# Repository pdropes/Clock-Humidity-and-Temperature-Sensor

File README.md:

# Clock, Humidity and Temperature Sensor
Relógio com medição de temperatura e humidade relativa

Descrição:
Pequeno aparelho portátil para visualização horária, temperatura e humidade relativa (alternadamente).
Já tinha trabalhado anteriormente com o sensor SHT21 da Sensirion, na construção de um controlador de estufa, é pequeno 3x3mm mas tem uma boa resolução (12/14bit for RH/T = RH0.04 & T0.01), apesar de fazer a leitura com esta precisão, uso aqui apenas uma casa decimal ás limitações do display.
Não foi implementado na programação medições de temperatura negativas, embora seja possível com outro tipo de display.
O sensor foi aqui montado numa placa á parte para minimizar a transferência térmica com a pcb principal (também sugerido na sua ficha técnica), entretanto a sua alimentação só é activada no momento das medições, reduz o consumo e tem maior precisão na leitura.
Desenho do circuito, fabrico da PCB, montagem e programação em 7 dias.

Caracteristicas:
- Microcontrolador atmega8 a 4MHz interno (não há necessidade de precisão aqui)
- Relógio RTC (PCF8563) com recurso a supercap 0.047F para retenção horária
- Possibilidade de acerto horário através dos switchs, modo ADC
- Sensor STH21 alimentado a 2.8V (VDD 2.1V to 3.6V), level shifter através de 2 BS170
- Consumo de 8 a 12mA (depende da intensidade do display)
- Brilho ajustável 

Programação: Bascom AVR, PCB: Eagle

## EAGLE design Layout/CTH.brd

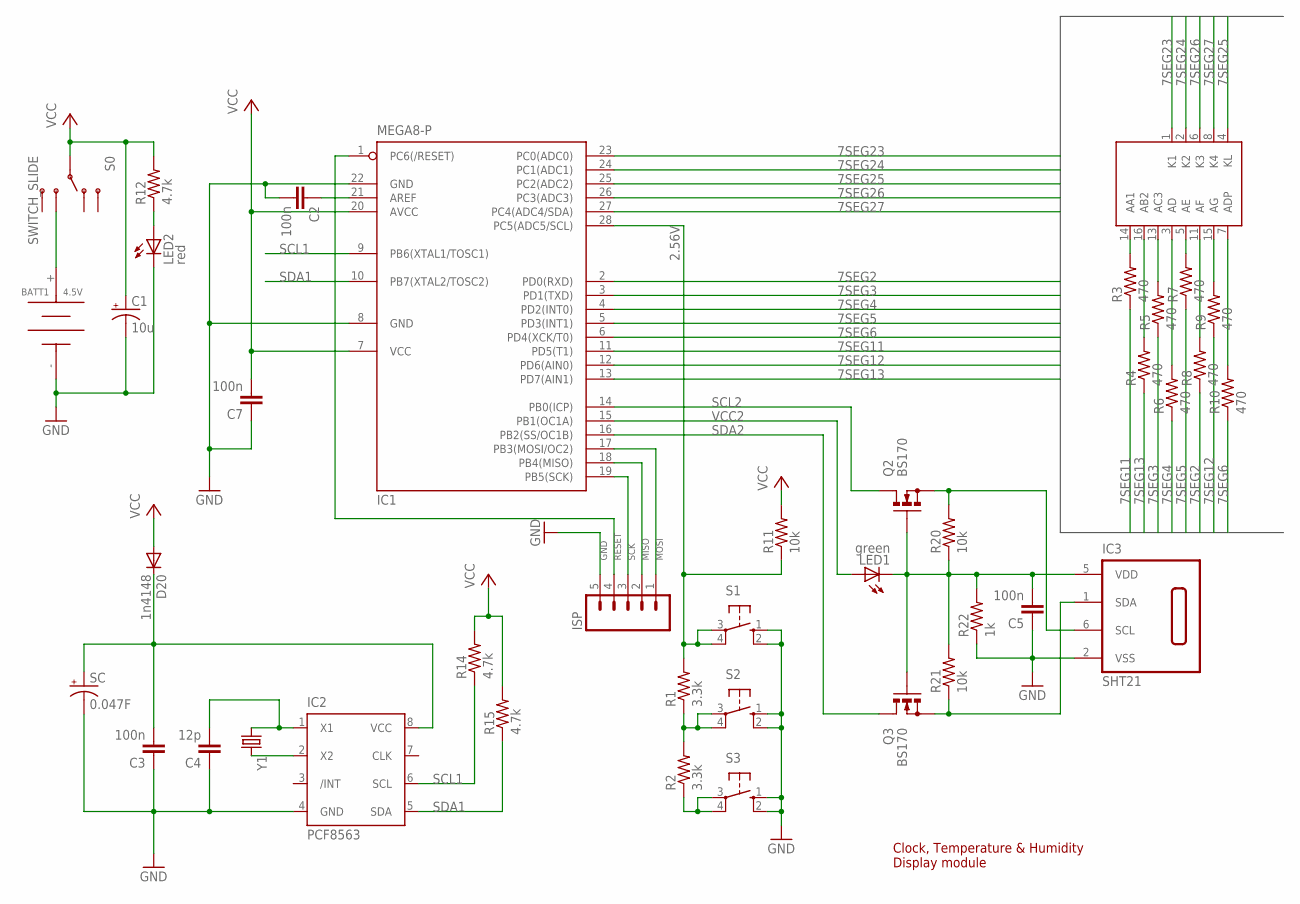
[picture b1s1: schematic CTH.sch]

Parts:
7SEG: LTC-4027JRLTC-4027JR; LTC-4727JR
BATT1: 1291-[2-56]; 1291
C1: 10u; CPOL-RADIAL-10UF-25V
C2, C3, C5, C7: 100n; 0805
C4: 12p; 0805
D20: 1n4148; SOD80C
IC1: MEGA8-P; DIL28-3
IC2: PCF8563; DS1307_PCF8583_DIL08
IC3: SHT21; DFN6/SHT
ISP: M05PTH; 1X05
LED1: green; SPARKFUN_LED-1206
LED2: red; LED3MM
Q2, Q3: BS170; SOT54E
R1, R2: 3.3k; 0805
R3, R4, R5, R6, R7, R8, R9, R10: 470; 0805
R11, R20, R21: 10k; 0805
R12, R14, R15: 4.7k; 0805
R22: 1k; 0805
S0: SWITCH_SLIDE
S1: 10-XX; B3F-10XX; MPN B3F-1000
S2, S3: 10-XX; B3F-10XX
SC: 0.047F; SUPERCAP_0.047F
Y1: CRYSTALTC38H; TC38H

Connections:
2.56V: IC1.28 (PC5(ADC5/SCL)), R1.2, R11.1, S1.3, S1.4 (P1)
7SEG2: IC1.2 (PD0(RXD)), R8.1
7SEG3: IC1.3 (PD1(TXD)), R5.1
7SEG4: IC1.4 (PD2(INT0)), R6.1
7SEG5: IC1.5 (PD3(INT1)), R7.1
7SEG6: IC1.6 (PD4(XCK/T0)), R10.1
7SEG11: IC1.11 (PD5(T1)), R3.1
7SEG12: IC1.12 (PD6(AIN0)), R9.1
7SEG13: IC1.13 (PD7(AIN1)), R4.1
7SEG23: 7SEG.1 (K1), IC1.23 (PC0(ADC0))
7SEG24: 7SEG.2 (K2), IC1.24 (PC1(ADC1))
7SEG25: 7SEG.4 (KL), IC1.25 (PC2(ADC2))
7SEG26: 7SEG.6 (K3), IC1.26 (PC3(ADC3))
7SEG27: 7SEG.8 (K4), IC1.27 (PC4(ADC4/SDA))
GND: BATT1.-, C1.2 (-), C2.2, C3.1, C4.1, C5.1, C7.1, IC1.8 (GND), IC1.22 (GND), IC2.4 (GND), IC3.2 (VSS), ISP.5, LED2.K (C), R22.1, S1.1 (S), S1.2 (S1), S2.1 (S), S2.2 (S1), S3.1 (S), S3.2 (S1), SC.2 (-)
MISO: IC1.18 (PB4(MISO)), ISP.2
MOSI: IC1.17 (PB3(MOSI/OC2)), ISP.1
unnamed: 7SEG.14 (AA1), R3.2
unnamed: 7SEG.16 (AB2), R4.2
unnamed: 7SEG.13 (AC3), R5.2
unnamed: BATT1.+, S0.E
unnamed: 7SEG.3 (AD), R6.2
unnamed: 7SEG.5 (AE), R7.2
unnamed: 7SEG.11 (AF), R8.2
unnamed: 7SEG.15 (AG), R9.2
unnamed: 7SEG.7 (ADP), R10.2
unnamed: IC2.2 (X2), Y1.2
unnamed: C2.1, IC1.21 (AREF)
unnamed: C5.2, IC3.5 (VDD), LED1.C, Q2.G, Q3.G, R20.1, R21.2, R22.2
unnamed: LED2.A, R12.1
unnamed: IC3.1 (SDA), Q3.S, R21.1
unnamed: R2.1, S3.3, S3.4 (P1)
unnamed: C4.2, IC2.1 (X1), Y1.1
unnamed: R1.1, R2.2, S2.3, S2.4 (P1)
unnamed: IC3.6 (SCL), Q2.S, R20.2
RESET: IC1.1 (PC6(/RESET)), ISP.4
SCK: IC1.19 (PB5(SCK)), ISP.3
SCL1: IC1.9 (PB6(XTAL1/TOSC1)), IC2.6 (SCL), R14.1
SCL2: IC1.14 (PB0(ICP)), Q2.D
SDA1: IC1.10 (PB7(XTAL2/TOSC2)), IC2.5 (SDA), R15.1
SDA2: IC1.16 (PB2(SS/OC1B)), Q3.D
VCC: C1.1 (+), C7.2, D20.A, IC1.7 (VCC), IC1.20 (AVCC), R11.2, R12.2, R14.2, R15.2, S0.M
VCC2: IC1.15 (PB1(OC1A)), LED1.A
VCC_RTC: C3.2, D20.C, IC2.8 (VCC), SC.1 (+)

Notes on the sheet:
Clock, Temperature & Humidity Display module

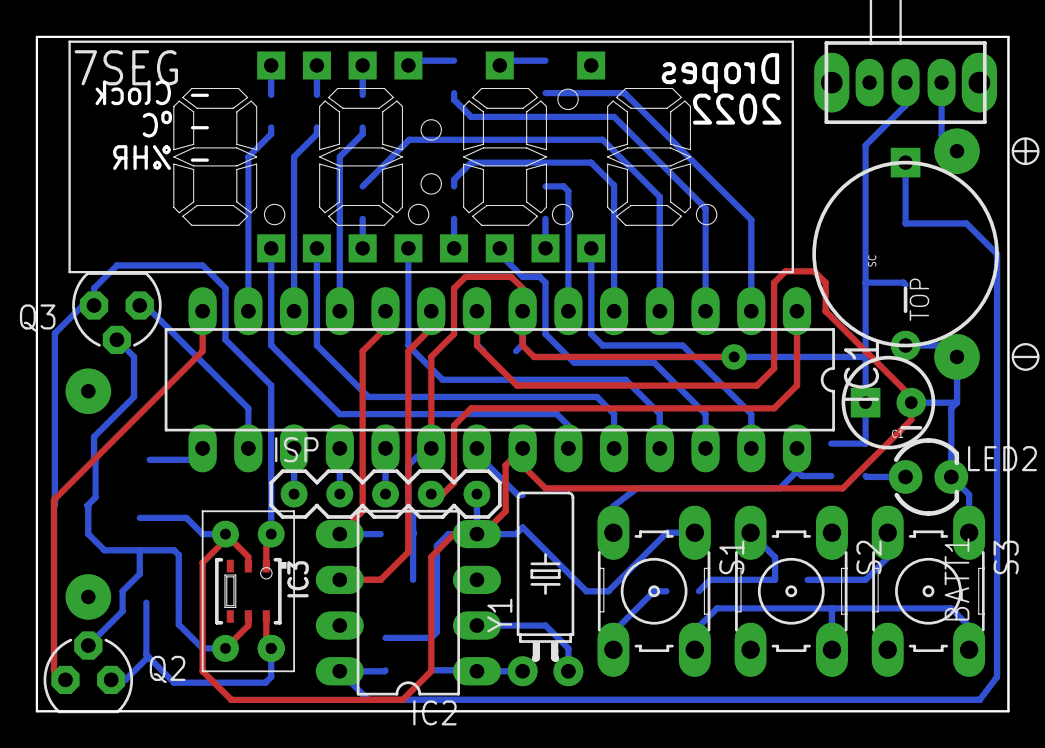
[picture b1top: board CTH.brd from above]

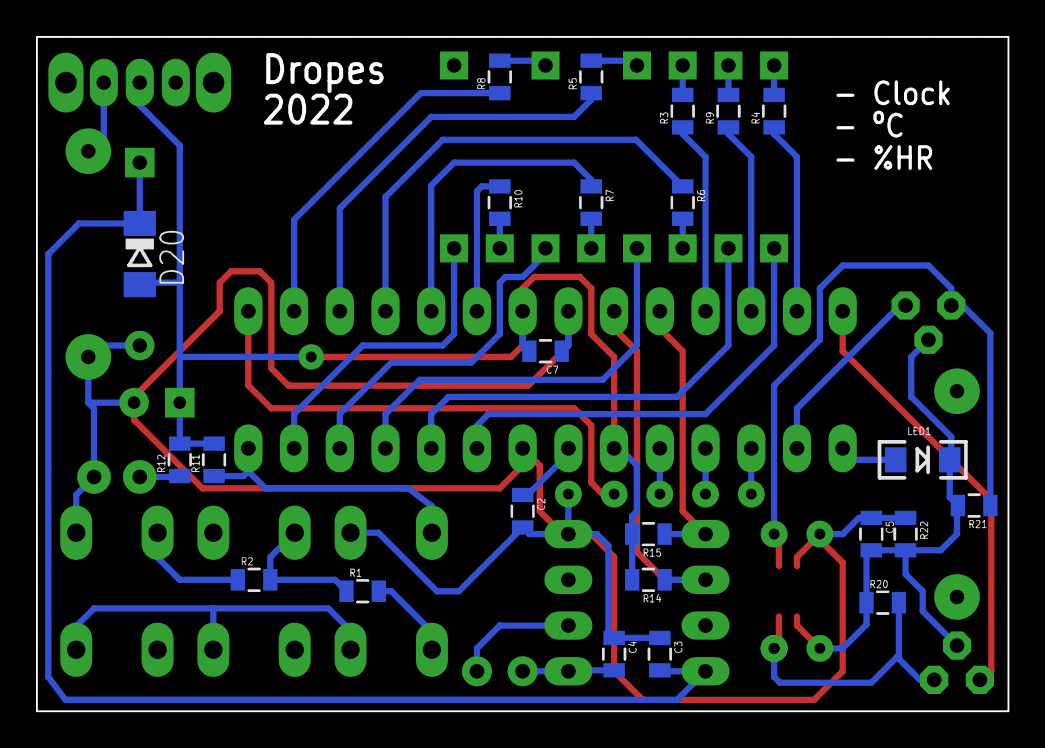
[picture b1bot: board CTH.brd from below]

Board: 2 copper layers, 54.0 x 37.5 mm, 40 parts (24 on the bottom side), 44 nets.

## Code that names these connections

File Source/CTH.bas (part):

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$framesize = 40                                             ' default use 40 for the frame space

'PIN        I/O   Func.      Func.
'09-PB6  O    SCL         RTC
'10-PB7  IO   SDA
'
'14.PB0  O    SCL2       SENSOR
'15.PB1  O    VCC2
'16.PB2  IO   SDA2

'23.PC0  O    7SEG_K1
'24.PC1  O    7SEG_K2
'25.PC2  O    7SEG_KL
'26.PC3  O    7SEG_K3
'27.PC4  O    7SEG_K4
'28.PC5  I      ADC5      SW1,2,3
'
'02.PD0  O     7SEG_F
'03.PD1  O     7SEG_C3
'04.PD2  O     7SEG_D
'05.PD3  O     7SEG_E
'06.PD4  O     7SEG_DP
'11.PD5  O     7SEG_A1
'12.PD6  O     7SEG_G
'13.PD7  O     7SEG_B2

'Digit nº
Ddrc = &B11011111
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

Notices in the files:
parts and their libraries:
SparkFun: Licensing: CC v3.0 Share-Alike You are welcome to use this library for commercial purposes.
sensirion: Copyright (C) 2011, Bob Starr
